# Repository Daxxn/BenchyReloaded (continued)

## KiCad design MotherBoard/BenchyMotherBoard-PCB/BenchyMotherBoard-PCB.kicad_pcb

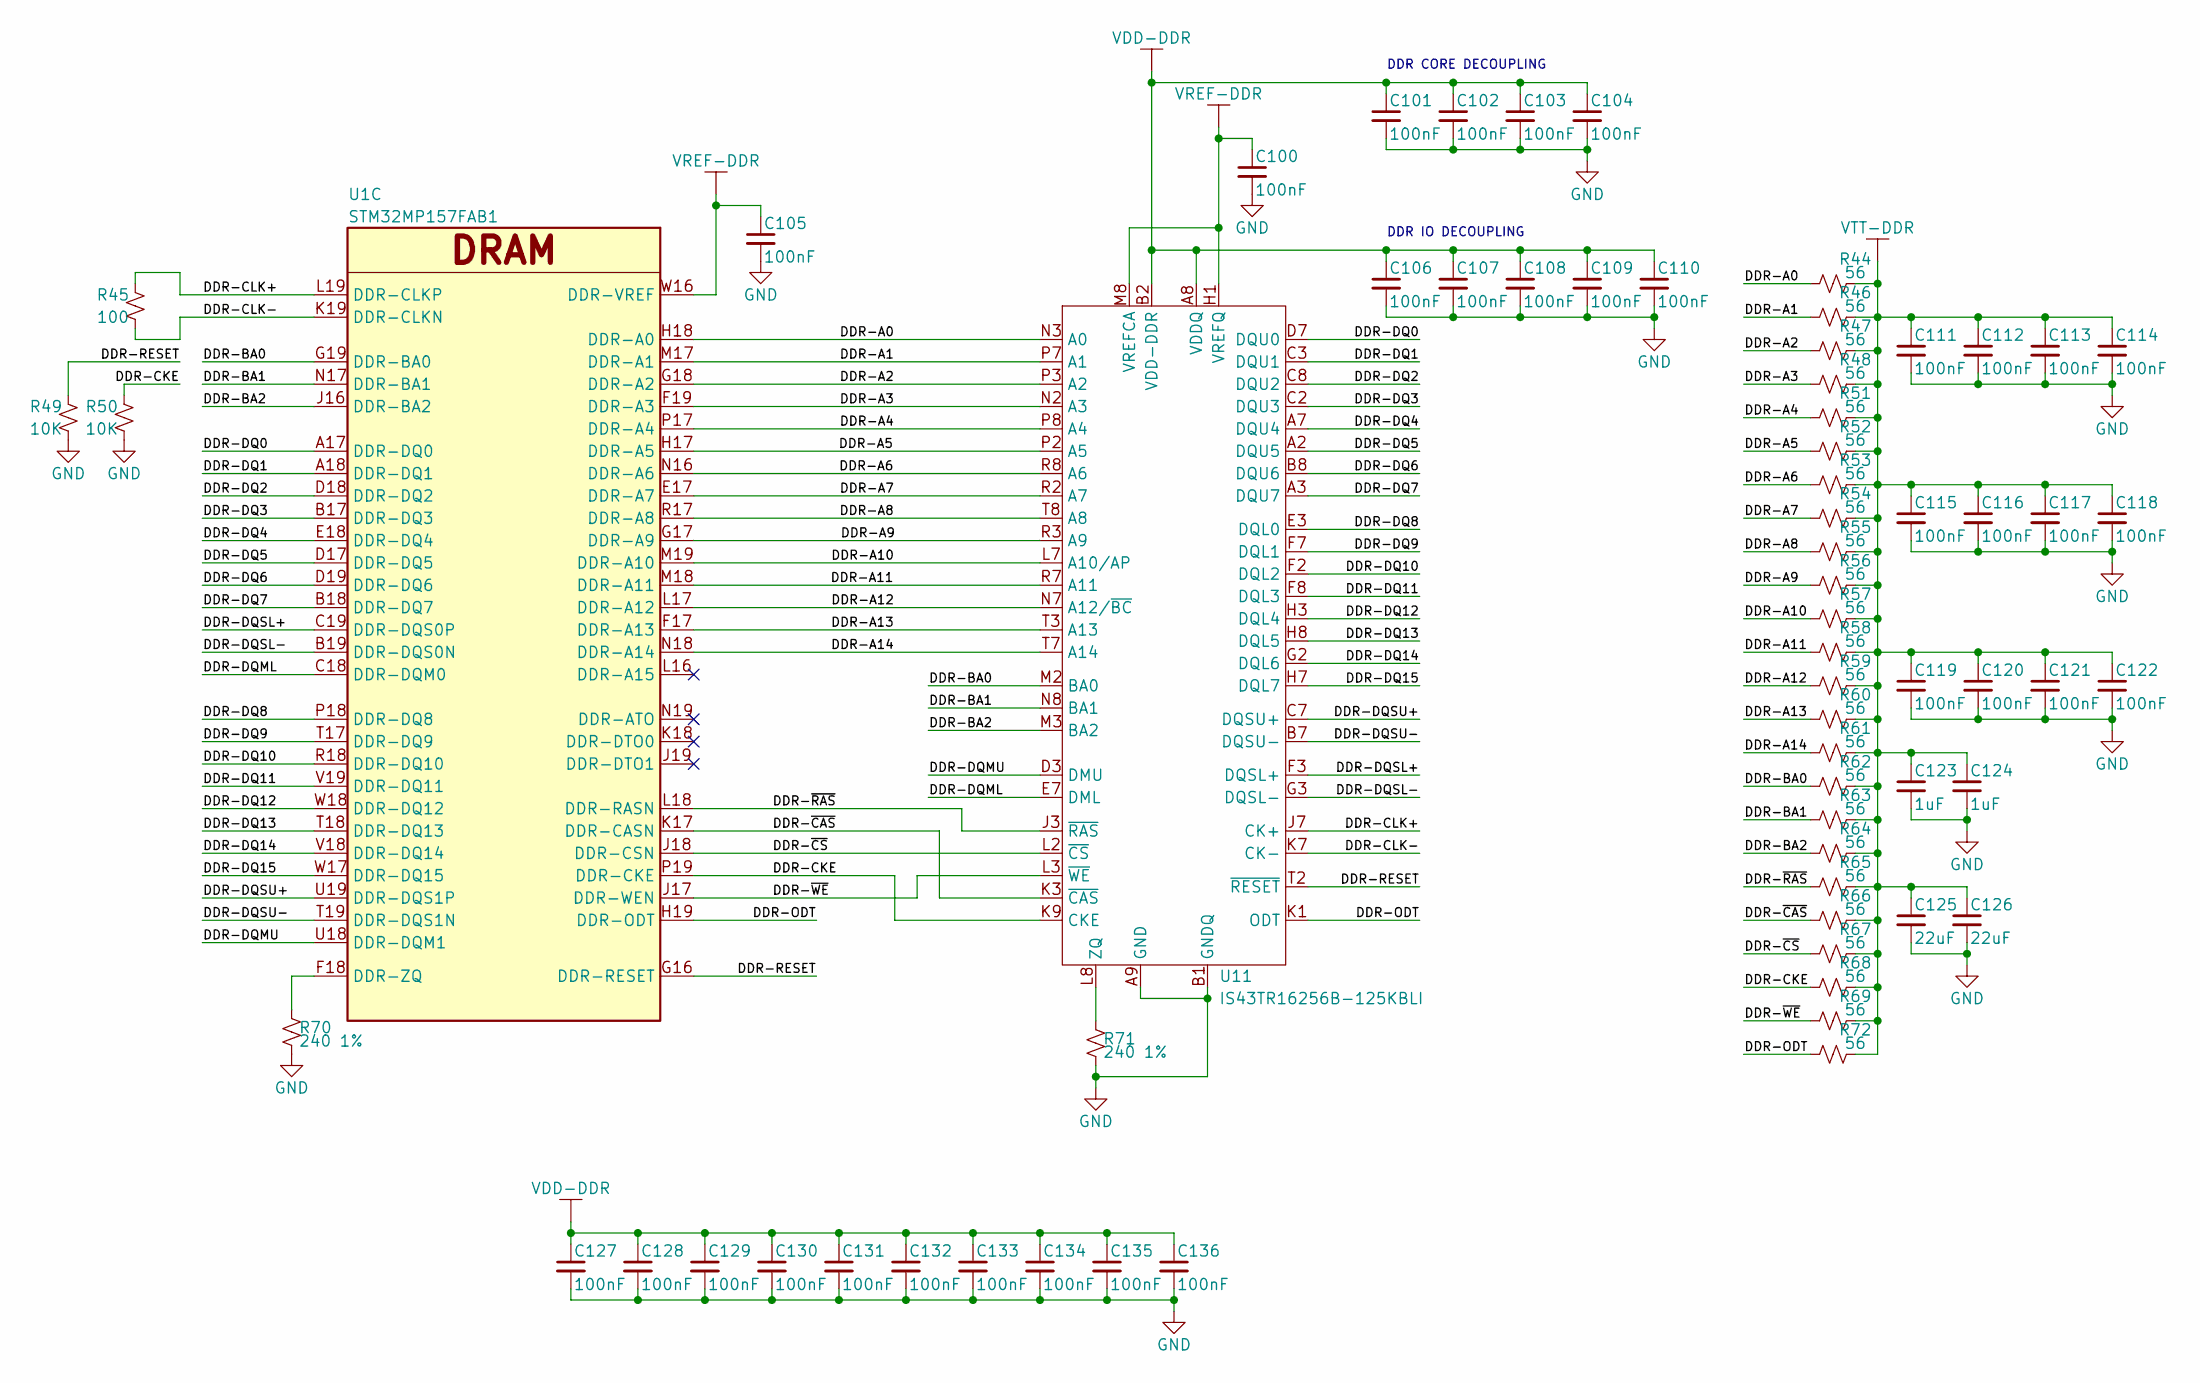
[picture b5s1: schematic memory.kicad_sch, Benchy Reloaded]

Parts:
C100, C105, C111, C112, C113, C114, C115, C116, C117, C118, C119, C120, C121, C122, C127, C128, C129, C130, C131, C132, C133, C134, C135, C136: 100nF; C_0402_1005Metric
C101, C102, C103, C104, C106, C107, C108, C109, C110: 100nF; C_0603_1608Metric
C123, C124: 1uF; C_0603_1608Metric
C125, C126: 22uF; C_1210_3225Metric
R44, R46, R47, R48, R51, R52, R53, R54, R55, R56, R57, R58, R59, R60, R61, R62, R63, R64, R65, R66, R67, R68, R69, R72: 56; R_0402_1005Metric
R45: 100; R_0402_1005Metric
R49, R50: 10K; R_0402_1005Metric
R70, R71: 240 1%; R_0402_1005Metric
U1: STM32MP157FAB1; LFBGA354-P0.8mm
U11: IS43TR16256B-125KBLI; BGA-96_9.0x13.0mm_Layout2x3x16_P0.8mm

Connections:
/MEMORY/DDR-A0: R44.1, U1.H18 (DDR-A0), U11.N3 (A0)
/MEMORY/DDR-A1: R46.1, U1.M17 (DDR-A1), U11.P7 (A1)
/MEMORY/DDR-A2: R47.1, U1.G18 (DDR-A2), U11.P3 (A2)
/MEMORY/DDR-A3: R48.1, U1.F19 (DDR-A3), U11.N2 (A3)
/MEMORY/DDR-A4: R51.1, U1.P17 (DDR-A4), U11.P8 (A4)
/MEMORY/DDR-A5: R52.1, U1.H17 (DDR-A5), U11.P2 (A5)
/MEMORY/DDR-A6: R53.1, U1.N16 (DDR-A6), U11.R8 (A6)
/MEMORY/DDR-A7: R54.1, U1.E17 (DDR-A7), U11.R2 (A7)
/MEMORY/DDR-A8: R55.1, U1.R17 (DDR-A8), U11.T8 (A8)
/MEMORY/DDR-A9: R56.1, U1.G17 (DDR-A9), U11.R3 (A9)
/MEMORY/DDR-A10: R57.1, U1.M19 (DDR-A10), U11.L7 (A10/AP)
/MEMORY/DDR-A11: R58.1, U1.M18 (DDR-A11), U11.R7 (A11)
/MEMORY/DDR-A12: R59.1, U1.L17 (DDR-A12), U11.N7 (A12/~BC)
/MEMORY/DDR-A13: R60.1, U1.F17 (DDR-A13), U11.T3 (A13)
/MEMORY/DDR-A14: R61.1, U1.N18 (DDR-A14), U11.T7 (A14)
/MEMORY/DDR-BA0: R62.1, U1.G19 (DDR-BA0), U11.M2 (BA0)
/MEMORY/DDR-BA1: R63.1, U1.N17 (DDR-BA1), U11.N8 (BA1)
/MEMORY/DDR-BA2: R64.1, U1.J16 (DDR-BA2), U11.M3 (BA2)
/MEMORY/DDR-CKE: R50.2, R68.1, U1.P19 (DDR-CKE), U11.K9 (CKE)
/MEMORY/DDR-CLK+: R45.2, U1.L19 (DDR-CLKP), U11.J7 (CK+)
/MEMORY/DDR-CLK-: R45.1, U1.K19 (DDR-CLKN), U11.K7 (CK-)
/MEMORY/DDR-DQ0: U1.A17 (DDR-DQ0), U11.D7 (DQU0)
/MEMORY/DDR-DQ1: U1.A18 (DDR-DQ1), U11.C3 (DQU1)
/MEMORY/DDR-DQ2: U1.D18 (DDR-DQ2), U11.C8 (DQU2)
/MEMORY/DDR-DQ3: U1.B17 (DDR-DQ3), U11.C2 (DQU3)
/MEMORY/DDR-DQ4: U1.E18 (DDR-DQ4), U11.A7 (DQU4)
/MEMORY/DDR-DQ5: U1.D17 (DDR-DQ5), U11.A2 (DQU5)
/MEMORY/DDR-DQ6: U1.D19 (DDR-DQ6), U11.B8 (DQU6)
/MEMORY/DDR-DQ7: U1.B18 (DDR-DQ7), U11.A3 (DQU7)
/MEMORY/DDR-DQ8: U1.P18 (DDR-DQ8), U11.E3 (DQL0)
/MEMORY/DDR-DQ9: U1.T17 (DDR-DQ9), U11.F7 (DQL1)
/MEMORY/DDR-DQ10: U1.R18 (DDR-DQ10), U11.F2 (DQL2)
/MEMORY/DDR-DQ11: U1.V19 (DDR-DQ11), U11.F8 (DQL3)
/MEMORY/DDR-DQ12: U1.W18 (DDR-DQ12), U11.H3 (DQL4)
/MEMORY/DDR-DQ13: U1.T18 (DDR-DQ13), U11.H8 (DQL5)
/MEMORY/DDR-DQ14: U1.V18 (DDR-DQ14), U11.G2 (DQL6)
/MEMORY/DDR-DQ15: U1.W17 (DDR-DQ15), U11.H7 (DQL7)
/MEMORY/DDR-DQML: U1.C18 (DDR-DQM0), U11.E7 (DML)
/MEMORY/DDR-DQMU: U1.U18 (DDR-DQM1), U11.D3 (DMU)
/MEMORY/DDR-DQSL+: U1.C19 (DDR-DQS0P), U11.F3 (DQSL+)
/MEMORY/DDR-DQSL-: U1.B19 (DDR-DQS0N), U11.G3 (DQSL-)
/MEMORY/DDR-DQSU+: U1.U19 (DDR-DQS1P), U11.C7 (DQSU+)
/MEMORY/DDR-DQSU-: U1.T19 (DDR-DQS1N), U11.B7 (DQSU-)
/MEMORY/DDR-ODT: R72.1, U1.H19 (DDR-ODT), U11.K1 (ODT)
/MEMORY/DDR-RESET: R49.2, U1.G16 (DDR-RESET), U11.T2 (~RESET)
/MEMORY/DDR-~CAS: R66.1, U1.K17 (DDR-CASN), U11.K3 (~CAS)
/MEMORY/DDR-~CS: R67.1, U1.J18 (DDR-CSN), U11.L2 (~CS)
/MEMORY/DDR-~RAS: R65.1, U1.L18 (DDR-RASN), U11.J3 (~RAS)
/MEMORY/DDR-~WE: R69.1, U1.J17 (DDR-WEN), U11.L3 (~WE)
GND: C100.2, C101.2, C102.2, C103.2, C104.2, C105.2, C106.2, C107.2, C108.2, C109.2, C110.2, C111.2, C112.2, C113.2, C114.2, C115.2, C116.2, C117.2, C118.2, C119.2, C120.2, C121.2, C122.2, C123.2, C124.2, C125.2, C126.2, C127.2, C128.2, C129.2, C130.2, C131.2, C132.2, C133.2, C134.2, C135.2, C136.2, R49.1, R50.1, R70.2, R71.2, U11.A9 (GND), U11.B1 (GNDQ), U11.B3 (GND), U11.B9 (GNDQ), U11.D1 (GNDQ), U11.D8 (GNDQ), U11.E1 (GND), U11.E2 (GNDQ), U11.E8 (GNDQ), U11.F9 (GNDQ), U11.G1 (GNDQ), U11.G8 (GND), U11.G9 (GNDQ), U11.J2 (GND), U11.J8 (GND), U11.M1 (GND), U11.M9 (GND), U11.N1 (GND), U11.P1 (GND), U11.P9 (GND), U11.T1 (GND), U11.T9 (GND); also elsewhere on the board
unnamed: R70.1, U1.F18 (DDR-ZQ)
unnamed: R71.1, U11.L8 (ZQ)
VDD-DDR: C101.1, C102.1, C103.1, C104.1, C106.1, C107.1, C108.1, C109.1, C110.1, C127.1, C128.1, C129.1, C130.1, C131.1, C132.1, C133.1, C134.1, C135.1, C136.1, U11.A1 (VDDQ), U11.A8 (VDDQ), U11.B2 (VDD-DDR), U11.C1 (VDDQ), U11.C9 (VDDQ), U11.D2 (VDDQ), U11.D9 (VDD-DDR), U11.E9 (VDDQ), U11.F1 (VDDQ), U11.G7 (VDD-DDR), U11.H2 (VDDQ), U11.H9 (VDDQ), U11.K2 (VDD-DDR), U11.K8 (VDD-DDR), U11.N9 (VDD-DDR), U11.R1 (VDD-DDR), U11.R9 (VDD-DDR); also elsewhere on the board
VREF-DDR: C100.1, C105.1, U1.W16 (DDR-VREF), U11.H1 (VREFQ), U11.M8 (VREFCA); also elsewhere on the board
VTT-DDR: C111.1, C112.1, C113.1, C114.1, C115.1, C116.1, C117.1, C118.1, C119.1, C120.1, C121.1, C122.1, C123.1, C124.1, C125.1, C126.1, R44.2, R46.2, R47.2, R48.2, R51.2, R52.2, R53.2, R54.2, R55.2, R56.2, R57.2, R58.2, R59.2, R60.2, R61.2, R62.2, R63.2, R64.2, R65.2, R66.2, R67.2, R68.2, R69.2, R72.2; also elsewhere on the board

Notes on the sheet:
DDR CORE DECOUPLING
DDR IO DECOUPLING

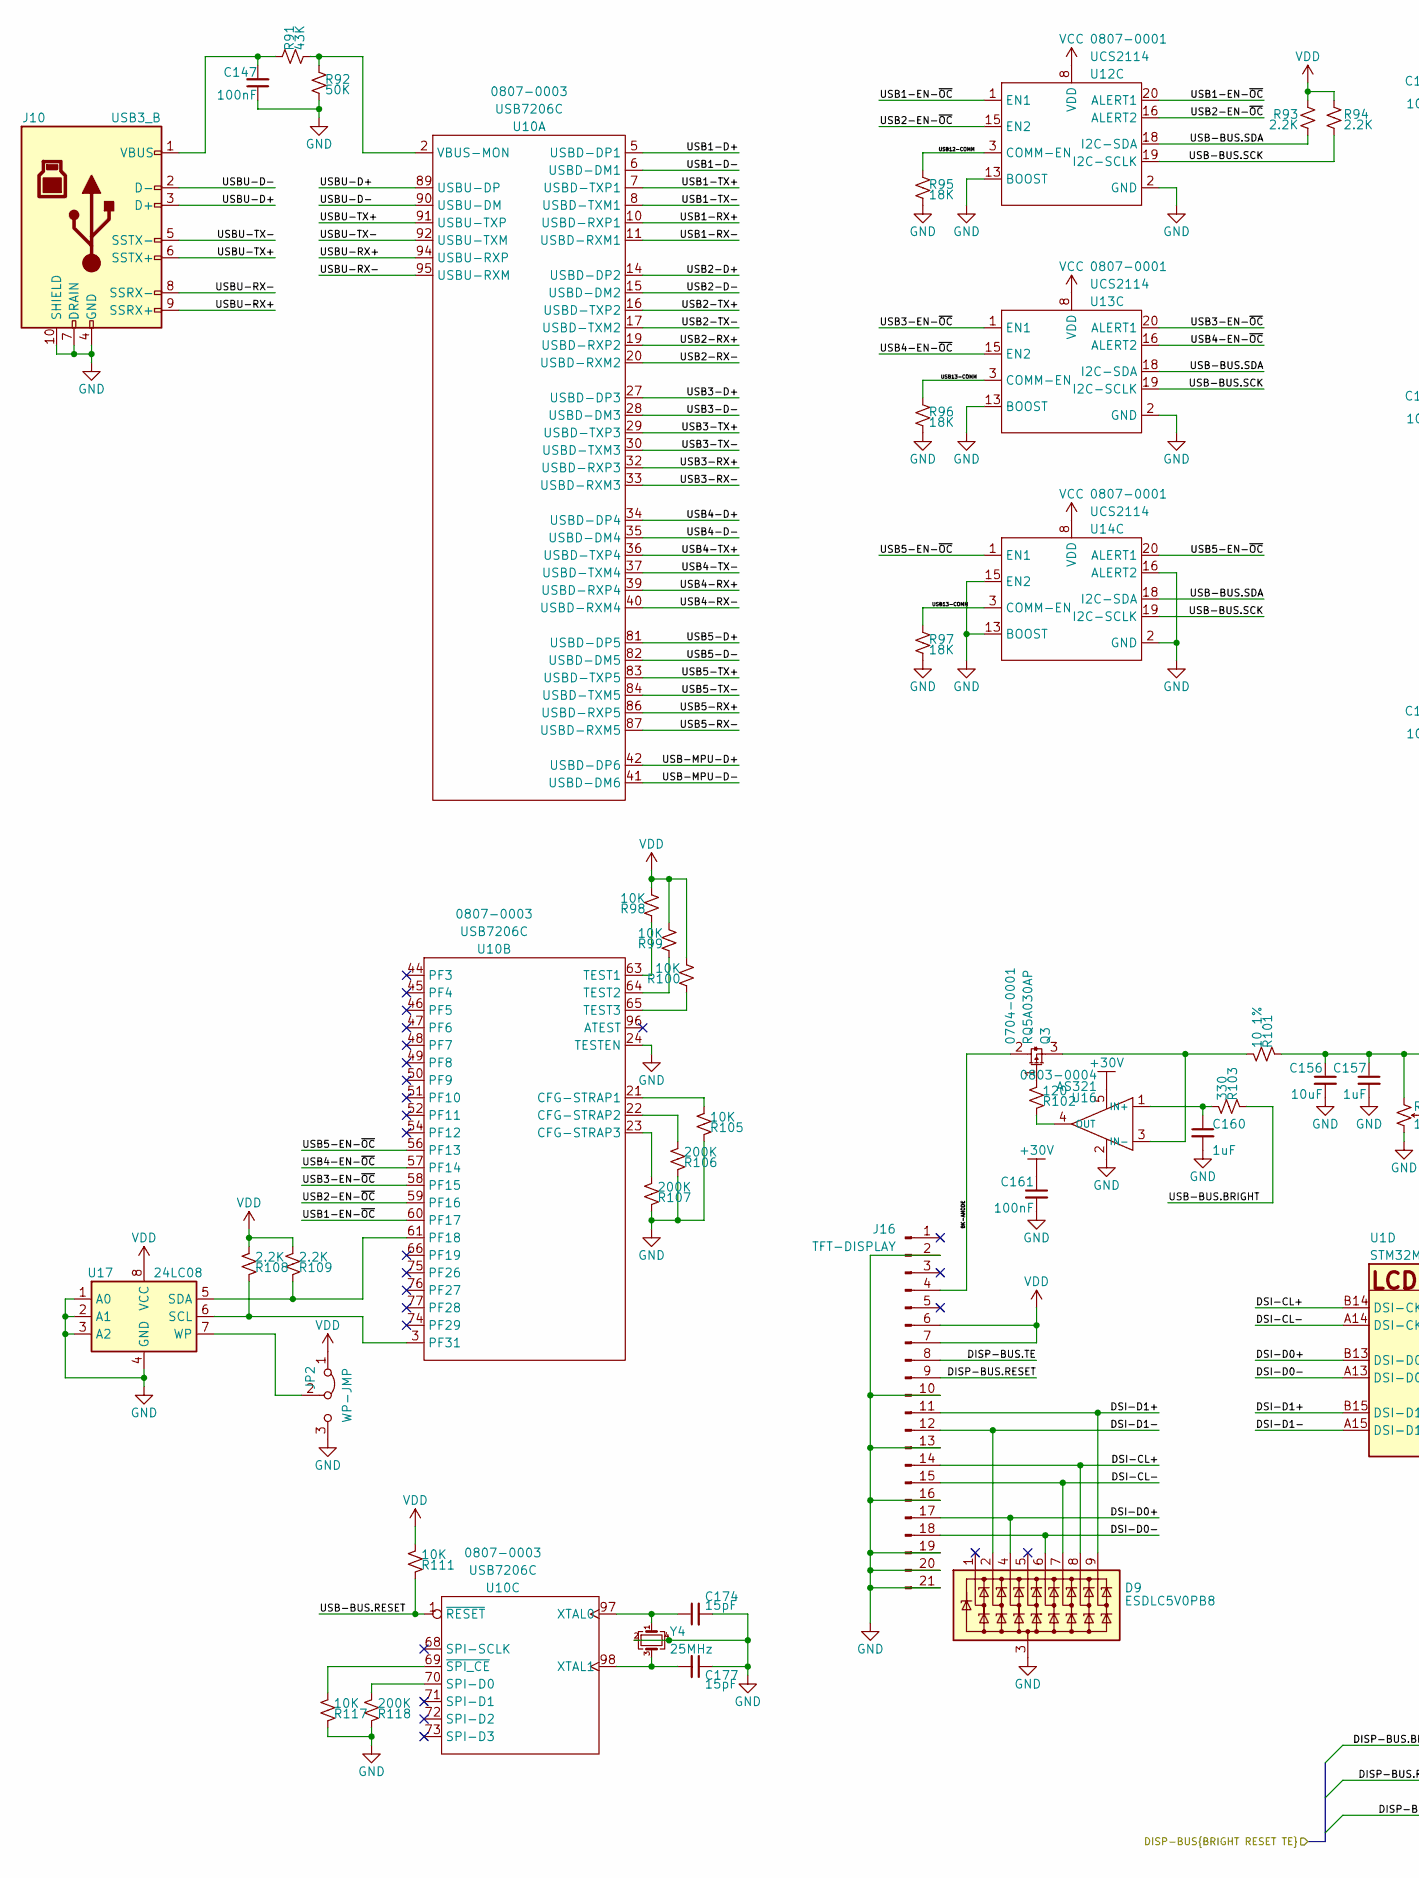
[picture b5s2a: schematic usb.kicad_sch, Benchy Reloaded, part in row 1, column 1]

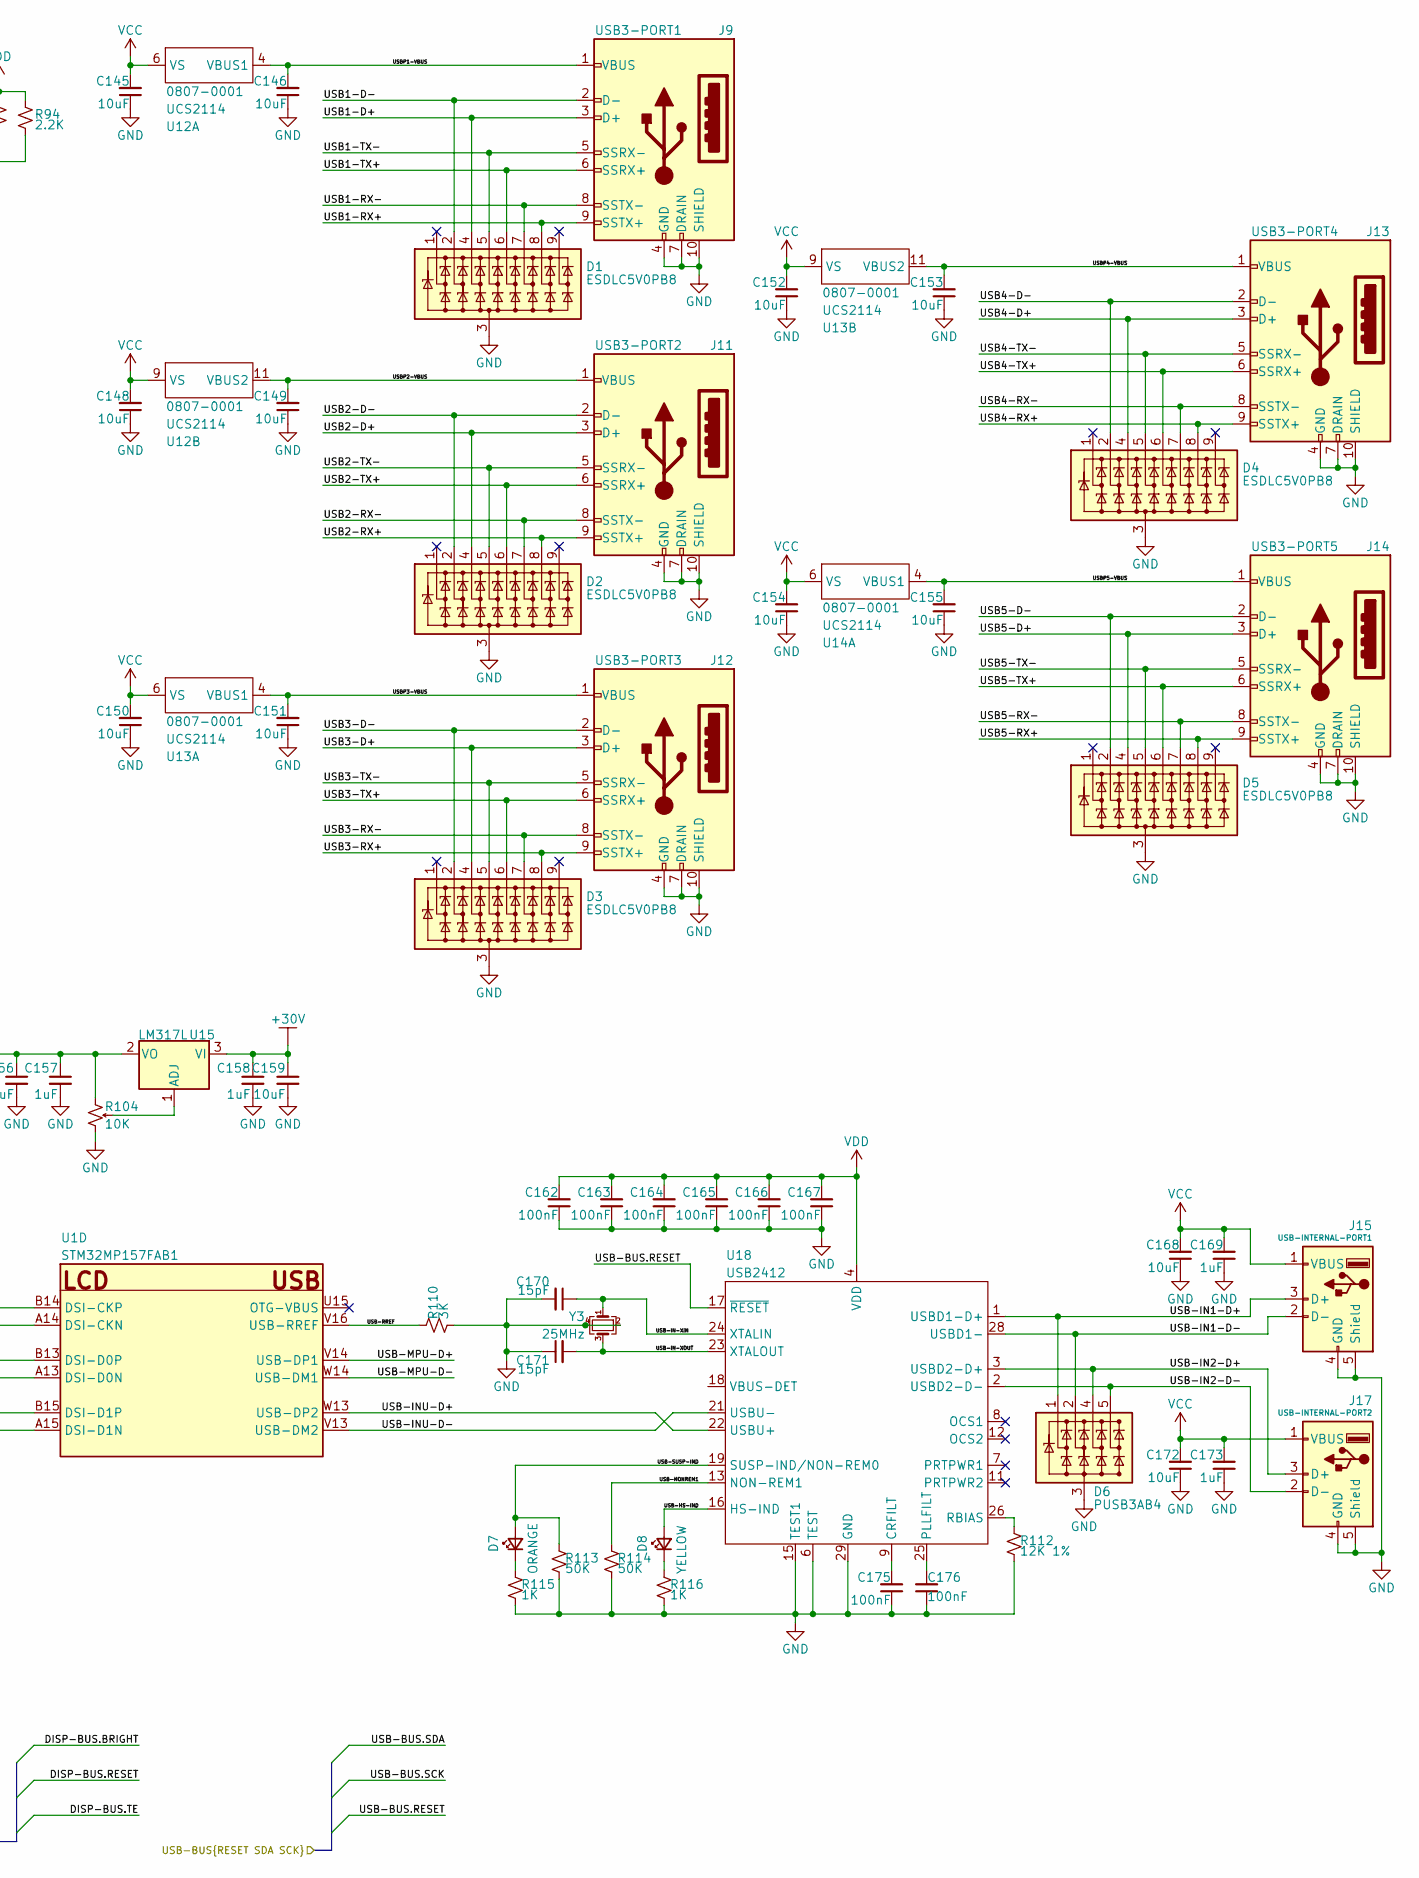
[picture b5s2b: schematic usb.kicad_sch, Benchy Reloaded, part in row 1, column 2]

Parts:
C145, C146, C148, C149, C150, C151, C152, C153, C154, C155, C156, C159, C168, C172: 10uF; C_1210_3225Metric
C147, C162, C163, C164, C165, C166, C167, C175, C176: 100nF; C_0402_1005Metric
C157, C158, C160: 1uF; C_0805_2012Metric
C161: 100nF; C_0805_2012Metric
C169, C173: 1uF; C_1210_3225Metric
C170, C171, C174, C177: 15pF; C_0402_1005Metric
D1, D2, D3, D4, D5, D9: ESDLC5V0PB8; UDFN-9_1.0x3.8mm_P0.5mm
D6: PUSB3AB4; DFN2510A-10
D7: ORANGE; LED-SMD-1204_RA
D8: YELLOW; LED-SMD-1204_RA
J9: USB3-PORT1; GSB4116341HR
J10: USB3_B; USB-GSB3211311WEU
J11: USB3-PORT2; GSB4116341HR
J12: USB3-PORT3; GSB4116341HR
J13: USB3-PORT4; GSB4116341HR
J14: USB3-PORT5; GSB4116341HR
J15: USB-INTERNAL-PORT1; 1002-014-01000
J16: TFT-DISPLAY; FH12A-20S-0.5SH55
J17: USB-INTERNAL-PORT2; 1002-014-01000
JP2: WP-JMP; PinSocket_1x03_P2.54mm_Vertical
Q3: RQ5A030AP; SOT-23; PartNumber 0704-0001
R91: 43K; R_0402_1005Metric
R92, R113, R114: 50K; R_0402_1005Metric
R93, R94, R108, R109: 2.2K; R_0402_1005Metric
R95, R96, R97: 18K; R_0402_1005Metric
R98, R99, R100, R105, R111, R117: 10K; R_0402_1005Metric
R101: 10 1%; R_0805_2012Metric
R102: 120; R_0805_2012Metric
R103: 330; R_0805_2012Metric
R104: 10K; Bourns_TC33X
R106, R107, R118: 200K; R_0402_1005Metric
R110: 3K; R_0402_1005Metric
R112: 12K 1%; R_0402_1005Metric
R115, R116: 1K; R_0402_1005Metric
U1: STM32MP157FAB1; LFBGA354-P0.8mm
U10: USB7206C; 100-VQFN-GND_12X12; PartNumber 0807-0003
U12, U13, U14: UCS2114; UCS2114T-1-V_LXVAO-Custom; PartNumber 0807-0001
U15: LM317L; SOT-89-3
U16: AS321; SOT-23-5; PartNumber 0803-0004
U17: 24LC08; SOIC-8_3.9x4.9mm_P1.27mm
U18: USB2412; QFN-28-1EP_5x5mm_P0.5mm_EP3.35x3.35mm
Y3, Y4: 25MHz; Crystal_SMD_4Pin_3.2x2.5mm

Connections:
+30V: C158.1, C159.1, C161.1, U15.3 (VI), U16.5 (V+); also elsewhere on the board
/INPUT | OUTPUT/DISP-BUS.RESET: J16.9; also elsewhere on the board
/INPUT | OUTPUT/DISP-BUS.TE: J16.8; also elsewhere on the board
/INPUT | OUTPUT/USB-BUS.RESET: R111.1, U10.1 (~RESET), U18.17 (~RESET); also elsewhere on the board
/INPUT | OUTPUT/USB-BUS.SCK: R94.2, U12.19 (I2C-SCLK), U13.19 (I2C-SCLK), U14.19 (I2C-SCLK); also elsewhere on the board
/INPUT | OUTPUT/USB-BUS.SDA: R93.2, U12.18 (I2C-SDA), U13.18 (I2C-SDA), U14.18 (I2C-SDA); also elsewhere on the board
/USB | DISPLAY/BK-ANODE: J16.4, Q3.2 (S)
/USB | DISPLAY/DSI-CL+: D9.8 (K7), J16.14, U1.B14 (DSI-CKP)
/USB | DISPLAY/DSI-CL-: D9.7 (K6), J16.15, U1.A14 (DSI-CKN)
/USB | DISPLAY/DSI-D0+: D9.4 (K3), J16.17, U1.B13 (DSI-D0P)
/USB | DISPLAY/DSI-D0-: D9.6 (K5), J16.18, U1.A13 (DSI-D0N)
/USB | DISPLAY/DSI-D1+: D9.9 (K8), J16.11, U1.B15 (DSI-D1P)
/USB | DISPLAY/DSI-D1-: D9.2 (K2), J16.12, U1.A15 (DSI-D1N)
/USB | DISPLAY/USB1-D+: D1.4 (K3), J9.3 (D+), U10.5 (USBD-DP1)
/USB | DISPLAY/USB1-D-: D1.2 (K2), J9.2 (D-), U10.6 (USBD-DM1)
/USB | DISPLAY/USB1-EN-~OC: U10.60 (PF17), U12.1 (EN1), U12.20 (ALERT1)
/USB | DISPLAY/USB1-RX+: D1.8 (K7), J9.9 (SSTX+), U10.10 (USBD-RXP1)
/USB | DISPLAY/USB1-RX-: D1.7 (K6), J9.8 (SSTX-), U10.11 (USBD-RXM1)
/USB | DISPLAY/USB1-TX+: D1.6 (K5), J9.6 (SSRX+), U10.7 (USBD-TXP1)
/USB | DISPLAY/USB1-TX-: D1.5 (K4), J9.5 (SSRX-), U10.8 (USBD-TXM1)
/USB | DISPLAY/USB2-D+: D2.4 (K3), J11.3 (D+), U10.14 (USBD-DP2)
/USB | DISPLAY/USB2-D-: D2.2 (K2), J11.2 (D-), U10.15 (USBD-DM2)
/USB | DISPLAY/USB2-EN-~OC: U10.59 (PF16), U12.15 (EN2), U12.16 (ALERT2)
/USB | DISPLAY/USB2-RX+: D2.8 (K7), J11.9 (SSTX+), U10.19 (USBD-RXP2)
/USB | DISPLAY/USB2-RX-: D2.7 (K6), J11.8 (SSTX-), U10.20 (USBD-RXM2)
/USB | DISPLAY/USB2-TX+: D2.6 (K5), J11.6 (SSRX+), U10.16 (USBD-TXP2)
/USB | DISPLAY/USB2-TX-: D2.5 (K4), J11.5 (SSRX-), U10.17 (USBD-TXM2)
/USB | DISPLAY/USB3-D+: D3.4 (K3), J12.3 (D+), U10.27 (USBD-DP3)
/USB | DISPLAY/USB3-D-: D3.2 (K2), J12.2 (D-), U10.28 (USBD-DM3)
/USB | DISPLAY/USB3-EN-~OC: U10.58 (PF15), U13.1 (EN1), U13.20 (ALERT1)
/USB | DISPLAY/USB3-RX+: D3.8 (K7), J12.9 (SSTX+), U10.32 (USBD-RXP3)
/USB | DISPLAY/USB3-RX-: D3.7 (K6), J12.8 (SSTX-), U10.33 (USBD-RXM3)
/USB | DISPLAY/USB3-TX+: D3.6 (K5), J12.6 (SSRX+), U10.29 (USBD-TXP3)
/USB | DISPLAY/USB3-TX-: D3.5 (K4), J12.5 (SSRX-), U10.30 (USBD-TXM3)
/USB | DISPLAY/USB4-D+: D4.4 (K3), J13.3 (D+), U10.34 (USBD-DP4)
/USB | DISPLAY/USB4-D-: D4.2 (K2), J13.2 (D-), U10.35 (USBD-DM4)
/USB | DISPLAY/USB4-EN-~OC: U10.57 (PF14), U13.15 (EN2), U13.16 (ALERT2)
/USB | DISPLAY/USB4-RX+: D4.8 (K7), J13.9 (SSTX+), U10.39 (USBD-RXP4)
/USB | DISPLAY/USB4-RX-: D4.7 (K6), J13.8 (SSTX-), U10.40 (USBD-RXM4)
/USB | DISPLAY/USB4-TX+: D4.6 (K5), J13.6 (SSRX+), U10.36 (USBD-TXP4)
/USB | DISPLAY/USB4-TX-: D4.5 (K4), J13.5 (SSRX-), U10.37 (USBD-TXM4)
/USB | DISPLAY/USB5-D+: D5.4 (K3), J14.3 (D+), U10.81 (USBD-DP5)
/USB | DISPLAY/USB5-D-: D5.2 (K2), J14.2 (D-), U10.82 (USBD-DM5)
/USB | DISPLAY/USB5-EN-~OC: U10.56 (PF13), U14.1 (EN1), U14.20 (ALERT1)
/USB | DISPLAY/USB5-RX+: D5.8 (K7), J14.9 (SSTX+), U10.86 (USBD-RXP5)
/USB | DISPLAY/USB5-RX-: D5.7 (K6), J14.8 (SSTX-), U10.87 (USBD-RXM5)
/USB | DISPLAY/USB5-TX+: D5.6 (K5), J14.6 (SSRX+), U10.83 (USBD-TXP5)
/USB | DISPLAY/USB5-TX-: D5.5 (K4), J14.5 (SSRX-), U10.84 (USBD-TXM5)
/USB | DISPLAY/USB12-COMM: R95.1, U12.3 (COMM-EN)
/USB | DISPLAY/USB13-COMM: R96.1, R97.1, U13.3 (COMM-EN), U14.3 (COMM-EN)
/USB | DISPLAY/USB-BUS.BRIGHT: R103.1
/USB | DISPLAY/USB-HS-IND: D8.2 (A), U18.16 (HS-IND)
/USB | DISPLAY/USB-IN1-D+: D6.1 (K1), J15.3 (D+), U18.1 (USBD1-D+)
/USB | DISPLAY/USB-IN1-D-: D6.2 (K2), J15.2 (D-), U18.28 (USBD1-)
/USB | DISPLAY/USB-IN2-D+: D6.4 (K3), J17.3 (D+), U18.3 (USBD2-D+)
/USB | DISPLAY/USB-IN2-D-: D6.5 (K4), J17.2 (D-), U18.2 (USBD2-D-)
/USB | DISPLAY/USB-IN-XIN: C170.1, U18.24 (XTALIN), Y3.1
/USB | DISPLAY/USB-IN-XOUT: C171.2, U18.23 (XTALOUT), Y3.3
/USB | DISPLAY/USB-INU-D+: U1.W13 (USB-DP2), U18.22 (USBU+)
/USB | DISPLAY/USB-INU-D-: U1.V13 (USB-DM2), U18.21 (USBU-)
/USB | DISPLAY/USB-MPU-D+: U1.V14 (USB-DP1), U10.42 (USBD-DP6)
/USB | DISPLAY/USB-MPU-D-: U1.W14 (USB-DM1), U10.41 (USBD-DM6)
/USB | DISPLAY/USB-NONREM1: R114.1, U18.13 (NON-REM1)
/USB | DISPLAY/USB-RREF: R110.1, U1.V16 (USB-RREF)
/USB | DISPLAY/USB-SUSP-IND: D7.2 (A), R113.1, U18.19 (SUSP-IND/NON-REM0)
/USB | DISPLAY/USBP1-VBUS: C146.2, J9.1 (VBUS), U12.4 (VBUS1), U12.5 (VBUS1)
/USB | DISPLAY/USBP2-VBUS: C149.2, J11.1 (VBUS), U12.11 (VBUS2), U12.12 (VBUS2)
/USB | DISPLAY/USBP3-VBUS: C151.2, J12.1 (VBUS), U13.4 (VBUS1), U13.5 (VBUS1)
/USB | DISPLAY/USBP4-VBUS: C153.2, J13.1 (VBUS), U13.11 (VBUS2), U13.12 (VBUS2)
/USB | DISPLAY/USBP5-VBUS: C155.2, J14.1 (VBUS), U14.4 (VBUS1), U14.5 (VBUS1)
/USB | DISPLAY/USBU-D+: J10.3 (D+), U10.89 (USBU-DP)
/USB | DISPLAY/USBU-D-: J10.2 (D-), U10.90 (USBU-DM)
/USB | DISPLAY/USBU-RX+: J10.9 (SSRX+), U10.94 (USBU-RXP)
/USB | DISPLAY/USBU-RX-: J10.8 (SSRX-), U10.95 (USBU-RXM)
/USB | DISPLAY/USBU-TX+: J10.6 (SSTX+), U10.91 (USBU-TXP)
/USB | DISPLAY/USBU-TX-: J10.5 (SSTX-), U10.92 (USBU-TXM)
GND: C145.1, C146.1, C147.1, C148.1, C149.1, C150.1, C151.1, C152.1, C153.1, C154.1, C155.1, C156.2, C157.2, C158.2, C159.2, C160.2, C161.2, C162.1, C163.1, C164.1, C165.1, C166.1, C167.1, C168.1, C169.1, C170.2, C171.1, C172.1, C173.1, C174.2, C175.1, C176.1, C177.1, D1.3 (A), D2.3 (A), D3.3 (A), D4.3 (A), D5.3 (A), D6.3 (A), D6.8 (A), D9.3 (A), J9.4 (GND), J9.7 (DRAIN), J9.10 (SHIELD), J10.4 (GND), J10.7 (DRAIN), J10.10 (SHIELD), J11.4 (GND), J11.7 (DRAIN), J11.10 (SHIELD), J12.4 (GND), J12.7 (DRAIN), J12.10 (SHIELD), J13.4 (GND), J13.7 (DRAIN), J13.10 (SHIELD), J14.4 (GND), J14.7 (DRAIN), J14.10 (SHIELD), J15.4 (GND), J15.5 (Shield), J16.2, J16.10, J16.13, J16.16, J16.19, J16.20, J16.21, J17.4 (GND), J17.5 (Shield), JP2.3 (B), R92.2, R95.2, R96.2, R97.2, R104.3, R105.1, R106.1, R107.1, R110.2, R112.2, R113.2, R114.2, R115.2, R116.2, R117.1, R118.1, U10.24 (TESTEN), U12.2 (GND), U12.13 (BOOST), U12.14 (GND), U12.17 (GND), U13.2 (GND), U13.13 (BOOST), U13.14 (GND), U13.17 (GND), U14.2 (GND), U14.13 (BOOST), U14.14 (GND), U14.15 (EN2), U14.16 (ALERT2), U14.17 (GND), U16.2 (V-), U17.1 (A0), U17.2 (A1), U17.3 (A2), U17.4 (GND), U18.6 (TEST), U18.15 (TEST1), U18.29 (GND), Y3.2, Y3.4, Y4.2, Y4.4; also elsewhere on the board
unnamed: C147.2, J10.1 (VBUS), R91.1
unnamed: C156.1, C157.1, R101.1, R104.1, U15.2 (VO)
unnamed: C160.1, R103.2, U16.1 (IN+)
unnamed: C174.1, U10.97 (XTAL0), Y4.1
unnamed: C175.2, U18.9 (CRFILT)
unnamed: C176.2, U18.25 (PLLFILT)
unnamed: C177.2, U10.98 (XTAL1), Y4.3
unnamed: D7.1 (K), R115.1
unnamed: D8.1 (K), R116.1
unnamed: JP2.2 (C), U17.7 (WP)
unnamed: Q3.1 (G), R102.2
unnamed: Q3.3 (D), R101.2, U16.3 (IN-)
unnamed: R91.2, R92.1, U10.2 (VBUS-MON)
unnamed: R98.1, U10.63 (TEST1)
unnamed: R99.1, U10.64 (TEST2)
unnamed: R100.1, U10.65 (TEST3)
unnamed: R102.1, U16.4 (OUT)
unnamed: R104.2, U15.1 (ADJ)
unnamed: R105.2, U10.21 (CFG-STRAP1)
unnamed: R106.2, U10.22 (CFG-STRAP2)
unnamed: R107.2, U10.23 (CFG-STRAP3)
unnamed: R108.1, U10.3 (PF31), U17.6 (SCL)
unnamed: R109.1, U10.61 (PF18), U17.5 (SDA)
unnamed: R112.1, U18.26 (RBIAS)
unnamed: R117.2, U10.69 (~SPI_CE)
unnamed: R118.2, U10.70 (SPI-D0)
VCC: C145.2, C148.2, C150.2, C152.2, C154.2, C168.2, C169.2, C172.2, C173.2, J15.1 (VBUS), J17.1 (VBUS), U12.6 (VS), U12.7 (VS), U12.8 (VDD), U12.9 (VS), U12.10 (VS), U13.6 (VS), U13.7 (VS), U13.8 (VDD), U13.9 (VS), U13.10 (VS), U14.6 (VS), U14.7 (VS), U14.8 (VDD); also elsewhere on the board
VDD: C162.2, C163.2, C164.2, C165.2, C166.2, C167.2, J16.6, J16.7, JP2.1 (A), R93.1, R94.1, R98.2, R99.2, R100.2, R108.2, R109.2, R111.2, U17.8 (VCC), U18.4 (VDD), U18.10 (VDD), U18.14 (VDD), U18.20 (VDD), U18.27 (VDD); also elsewhere on the board
